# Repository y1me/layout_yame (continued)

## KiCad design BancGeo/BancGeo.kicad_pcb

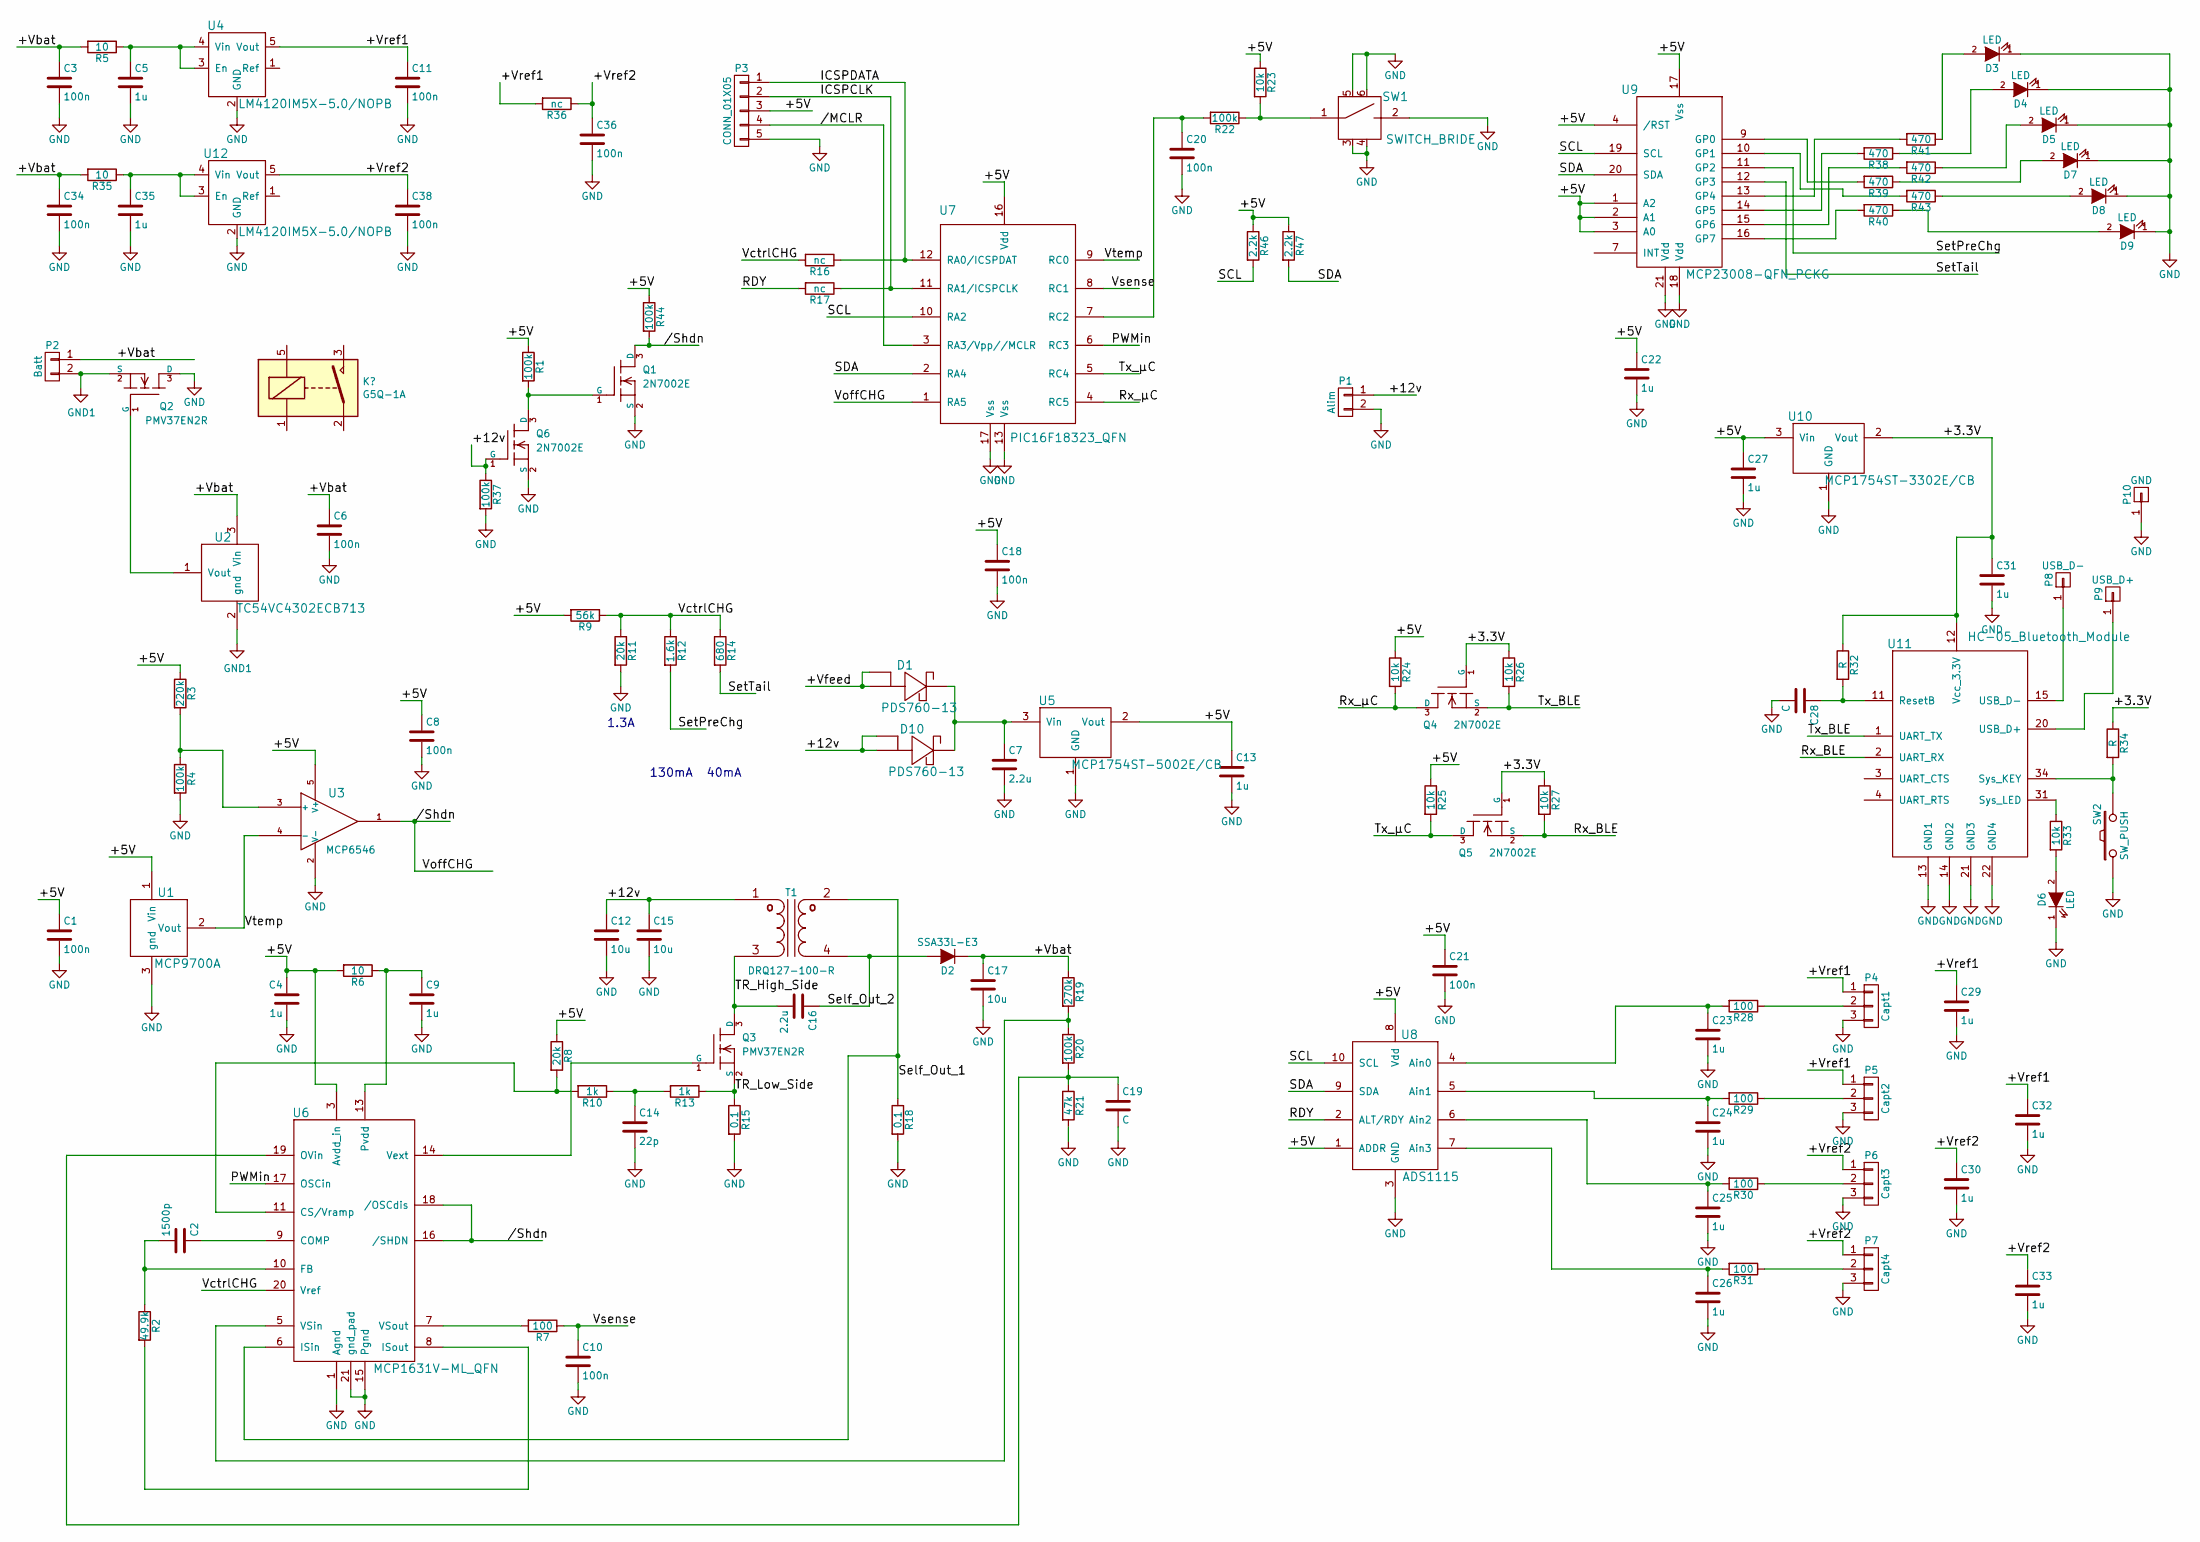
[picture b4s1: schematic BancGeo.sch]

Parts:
C1, C3, C6, C8, C10, C11, C18, C20, C21, C34, C36, C38: 100n; SM0603-MR
C2: 1500p; SM0603-MR
C4, C5, C9, C13, C22, C23, C24, C25, C26, C27, C29, C30, C31, C32, C33, C35: 1u; SM0805-MR
C7, C16: 2.2u; SM0805-MR
C12, C15, C17: 10u; SM0805-MR
C14: 22p; SM0603-MR
C19, C28: C; SM0603-MR
D1, D10: PDS760-13
D2: SSA33L-E3; DO-214AC
D3, D4, D5, D7, D8, D9: LED; LED-5MM_center
D6: LED; LED_0603
P1: Alim; PINHEAD1-2
P2: Batt; PINHEAD1-2
P3: CONN_01X05; HE10_14-5C-2.54-MR
P4: Capt1; PINHEAD1-3
P5: Capt2; PINHEAD1-3
P6: Capt3; PINHEAD1-3
P7: Capt4; PINHEAD1-3
P8: USB_D-; Test_Point_T_H
P9: USB_D+; Test_Point_T_H
P10: GND; Test_Point_T_H
Q1, Q4, Q5, Q6: 2N7002E; SOT23-MR
Q2, Q3: PMV37EN2R; SOT23-MR
R1, R4, R20, R22, R37, R44: 100k; SM0603-MR
R2: 49.9k; SM0603-MR
R3: 220k; SM0603-MR
R5, R6, R35: 10; SM0603-MR
R7, R28, R29, R30, R31: 100; SM0603-MR
R8, R11: 20k; SM0603-MR
R9: 56k; SM0603-MR
R10, R13: 1k; SM0603-MR
R12: 1.6k; SM0603-MR
R14: 680; SM0603-MR
R15, R18: 0.1; SM0603-MR
R16, R17, R36: nc; SM0603-MR
R19: 270k; SM0603-MR
R21: 47k; SM0603-MR
R23, R24, R25, R26, R27, R33: 10k; SM0603-MR
R32, R34: R; SM0603-MR
R38, R39, R40, R41, R42, R43: 470; SM0603-MR
R46, R47: 2.2k
SW1: SWITCH_BRIDE
SW2: SW_PUSH; SW_SPST_B3U-1000P
T1: DRQ127-100-R; DRQ127_CPL_TR
U1: MCP9700A; SOT23-MR
U2: TC54VC4302ECB713; SOT23-MR
U3: MCP6546; SOT23-5-MR
U4, U12: LM4120IM5X-5.0/NOPB; SOT-23-5
U5: MCP1754ST-5002E/CB; SOT23-MR
U6: MCP1631V-ML_QFN; QFN-20-1EP_4x4mm_Pitch0.5mm
U7: PIC16F18323_QFN; QFN-16-1EP_4x4mm_Pitch0.65mm
U8: ADS1115; TSSOP-10_3x3mm_Pitch0.5mm
U9: MCP23008-QFN_PCKG
U10: MCP1754ST-3302E/CB; SOT23-MR
U11: HC-05_Bluetooth_Module

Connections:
/+3.3V: C31.1, Q4.1 (G), Q5.1 (G), R26.1, R27.1, R32.1, R34.1, U10.2 (Vout), U11.12 (Vcc_3.3V)
/+5V: C1.1, C4.1, C8.1, C13.1, C18.1, C21.1, C22.1, C27.1, P3.3, R1.1, R3.1, R6.2, R8.1, R9.2, R23.1, R24.1, R25.1, R44.1, R46.1, R47.1, U1.1 (Vin), U3.5 (V+), U5.2 (Vout), U6.3 (Avdd_in), U7.16 (Vdd), U8.1 (ADDR), U8.8 (Vdd), U9.1 (A2), U9.2 (A1), U9.3 (A0), U9.4 (/RST), U9.17 (Vss), U10.3 (Vin)
/+12v: C12.1, C15.1, D10.A1 (A), D10.A2 (A), P1.1, Q6.1 (G), R37.1, T1.1 (AA)
/+Vbat: C3.1, C6.1, C17.1, C34.1, D2.1 (K), P2.1, R5.2, R19.1, R35.2, U2.3 (Vin)
/+Vref1: C11.1, C29.1, C32.1, P4.1, P5.1, R36.2, U4.5 (Vout)
/+Vref2: C30.1, C33.1, C36.1, C38.1, P6.1, P7.1, R36.1, U12.5 (Vout)
//MCLR: P3.4, U7.3 (RA3/Vpp//MCLR)
//Shdn: Q1.3 (D), R44.2, U3.1, U6.16 (/SHDN), U6.18 (/OSCdis), U7.1 (RA5)
/ICSPCLK: P3.2, R17.1, U7.11 (RA1/ICSPCLK)
/ICSPDATA: P3.1, R16.1, U7.12 (RA0/ICSPDAT)
/PWMin: U6.17 (OSCin), U7.6 (RC3)
/RDY: R17.2, U8.2 (ALT/RDY)
/Rx_BLE: Q5.2 (S), R27.2, U11.2 (UART_RX)
/Rx_µC: Q4.3 (D), R24.2, U7.4 (RC5)
/SCL: R46.2, U7.10 (RA2), U8.10 (SCL), U9.19 (SCL)
/SDA: R47.2, U7.2 (RA4), U8.9 (SDA), U9.20 (SDA)
/Self_Out_1: R18.1, T1.2 (SB), U6.6 (ISin)
/Self_Out_2: C16.1, D2.2 (A), T1.4 (SA)
/SetPreChg: R12.2, U9.11 (GP2)
/SetTail: R14.2, U9.12 (GP3)
/TR_High_Side: C16.2, Q3.3 (D), T1.3 (AB)
/TR_Low_Side: Q3.2 (S), R13.1, R15.1
/Tx_BLE: Q4.2 (S), R26.2, U11.1 (UART_TX)
/Tx_µC: Q5.3 (D), R25.2, U7.5 (RC4)
/VctrlCHG: R9.1, R11.1, R12.1, R14.1, R16.2, U6.20 (Vref)
/Vsense: C10.1, R7.1, U7.8 (RC1)
/Vtemp: U1.2 (Vout), U3.4 (-), U7.9 (RC0)
unnamed: C2.1, U6.9 (COMP)
unnamed: C2.2, R2.1, U6.10 (FB)
unnamed: C5.1, R5.1, U4.3 (En), U4.4 (Vin)
unnamed: C7.1, D1.K, D10.K, U5.3 (Vin)
unnamed: C9.1, R6.1, U6.13 (Pvdd)
unnamed: C14.1, R10.1, R13.2
unnamed: C19.1, R20.2, R21.1, U6.19 (OVin)
unnamed: C20.1, R22.2, U7.7 (RC2)
unnamed: C23.1, R28.2, U8.4 (Ain0)
unnamed: C24.1, R29.2, U8.5 (Ain1)
unnamed: C25.1, R30.2, U8.6 (Ain2)
unnamed: C26.1, R31.2, U8.7 (Ain3)
unnamed: C28.1, R32.2, U11.11 (ResetB)
unnamed: C35.1, R35.1, U12.3 (En), U12.4 (Vin)
unnamed: D1.A1 (A), D1.A2 (A)
unnamed: D3.2 (A), R41.1
unnamed: D4.2 (A), R38.1
unnamed: D5.2 (A), R42.1
unnamed: D6.2 (A), R33.2
unnamed: D7.2 (A), R39.1
unnamed: D8.2 (A), R43.1
unnamed: D9.2 (A), R40.1
unnamed: P4.2, R28.1
unnamed: P5.2, R29.1
unnamed: P6.2, R30.1
unnamed: P7.2, R31.1
unnamed: P8.1, U11.15 (USB_D-)
unnamed: P9.1, U11.20 (USB_D+)
unnamed: Q1.1 (G), Q6.3 (D), R1.2
unnamed: Q2.1 (G), U2.1 (Vout)
unnamed: Q3.1 (G), U6.14 (Vext)
unnamed: R2.2, U6.8 (ISout)
unnamed: R3.2, R4.1, U3.3 (+)
unnamed: R7.2, U6.7 (VSout)
unnamed: R8.2, R10.2, U6.11 (CS/Vramp)
unnamed: R19.2, R20.1, U6.5 (VSin)
unnamed: R22.1, R23.2, SW1.1
unnamed: R33.1, U11.31 (Sys_LED)
unnamed: R34.2, SW2.2, U11.34 (Sys_KEY)
unnamed: R38.2, U9.14 (GP5)
unnamed: R39.2, U9.9 (GP0)
unnamed: R40.2, U9.16 (GP7)
unnamed: R41.2, U9.13 (GP4)
unnamed: R42.2, U9.15 (GP6)
unnamed: R43.2, U9.10 (GP1)

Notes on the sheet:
1.3A
130mA
40mA

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
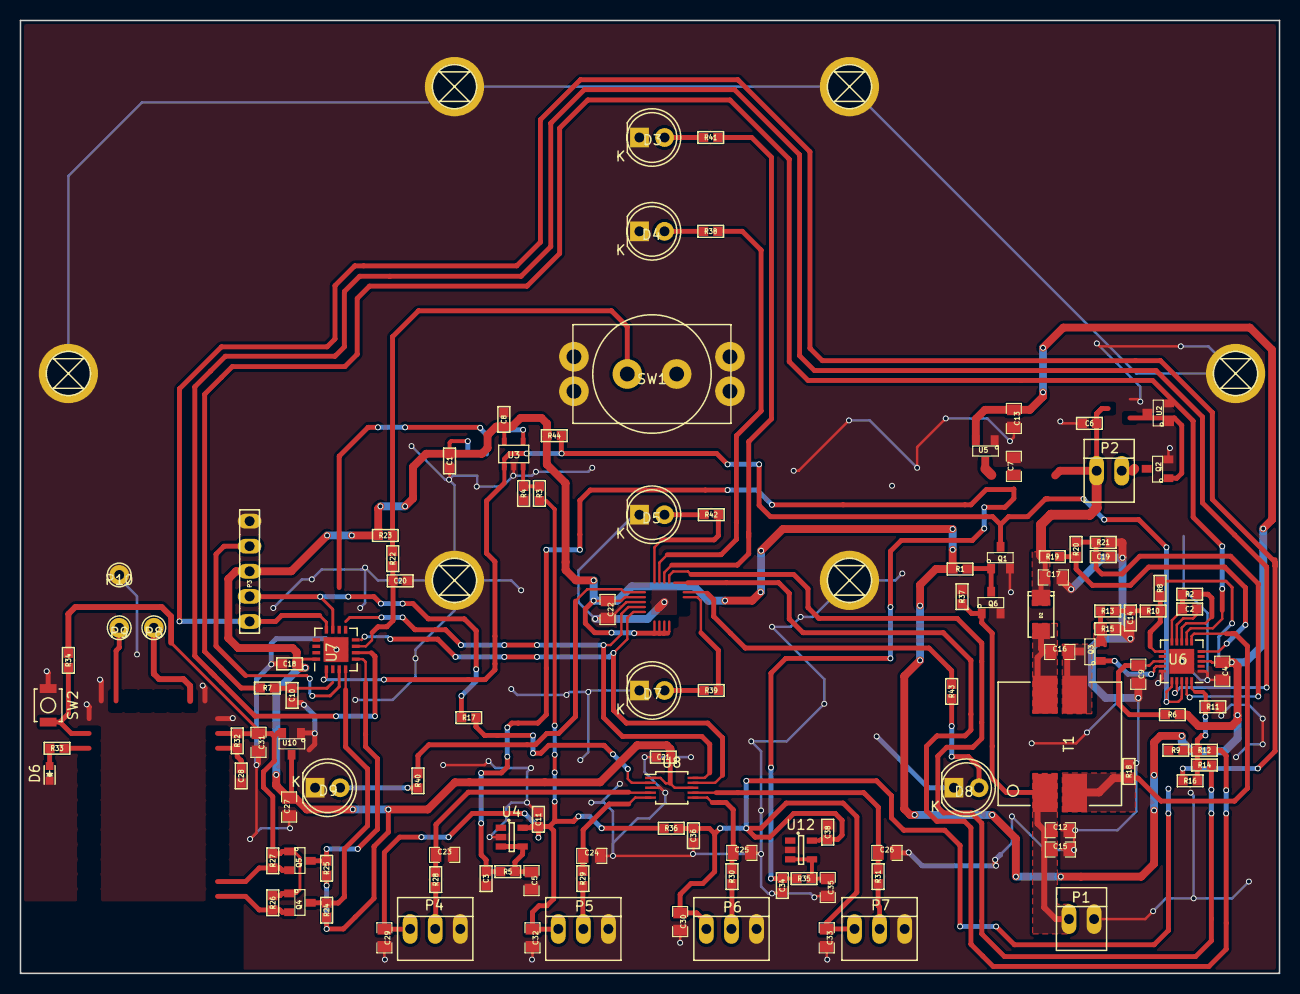
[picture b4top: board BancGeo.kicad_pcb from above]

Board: 2 copper layers, 127.5 x 96.5 mm, 118 parts (1 on the bottom side), 61 nets.

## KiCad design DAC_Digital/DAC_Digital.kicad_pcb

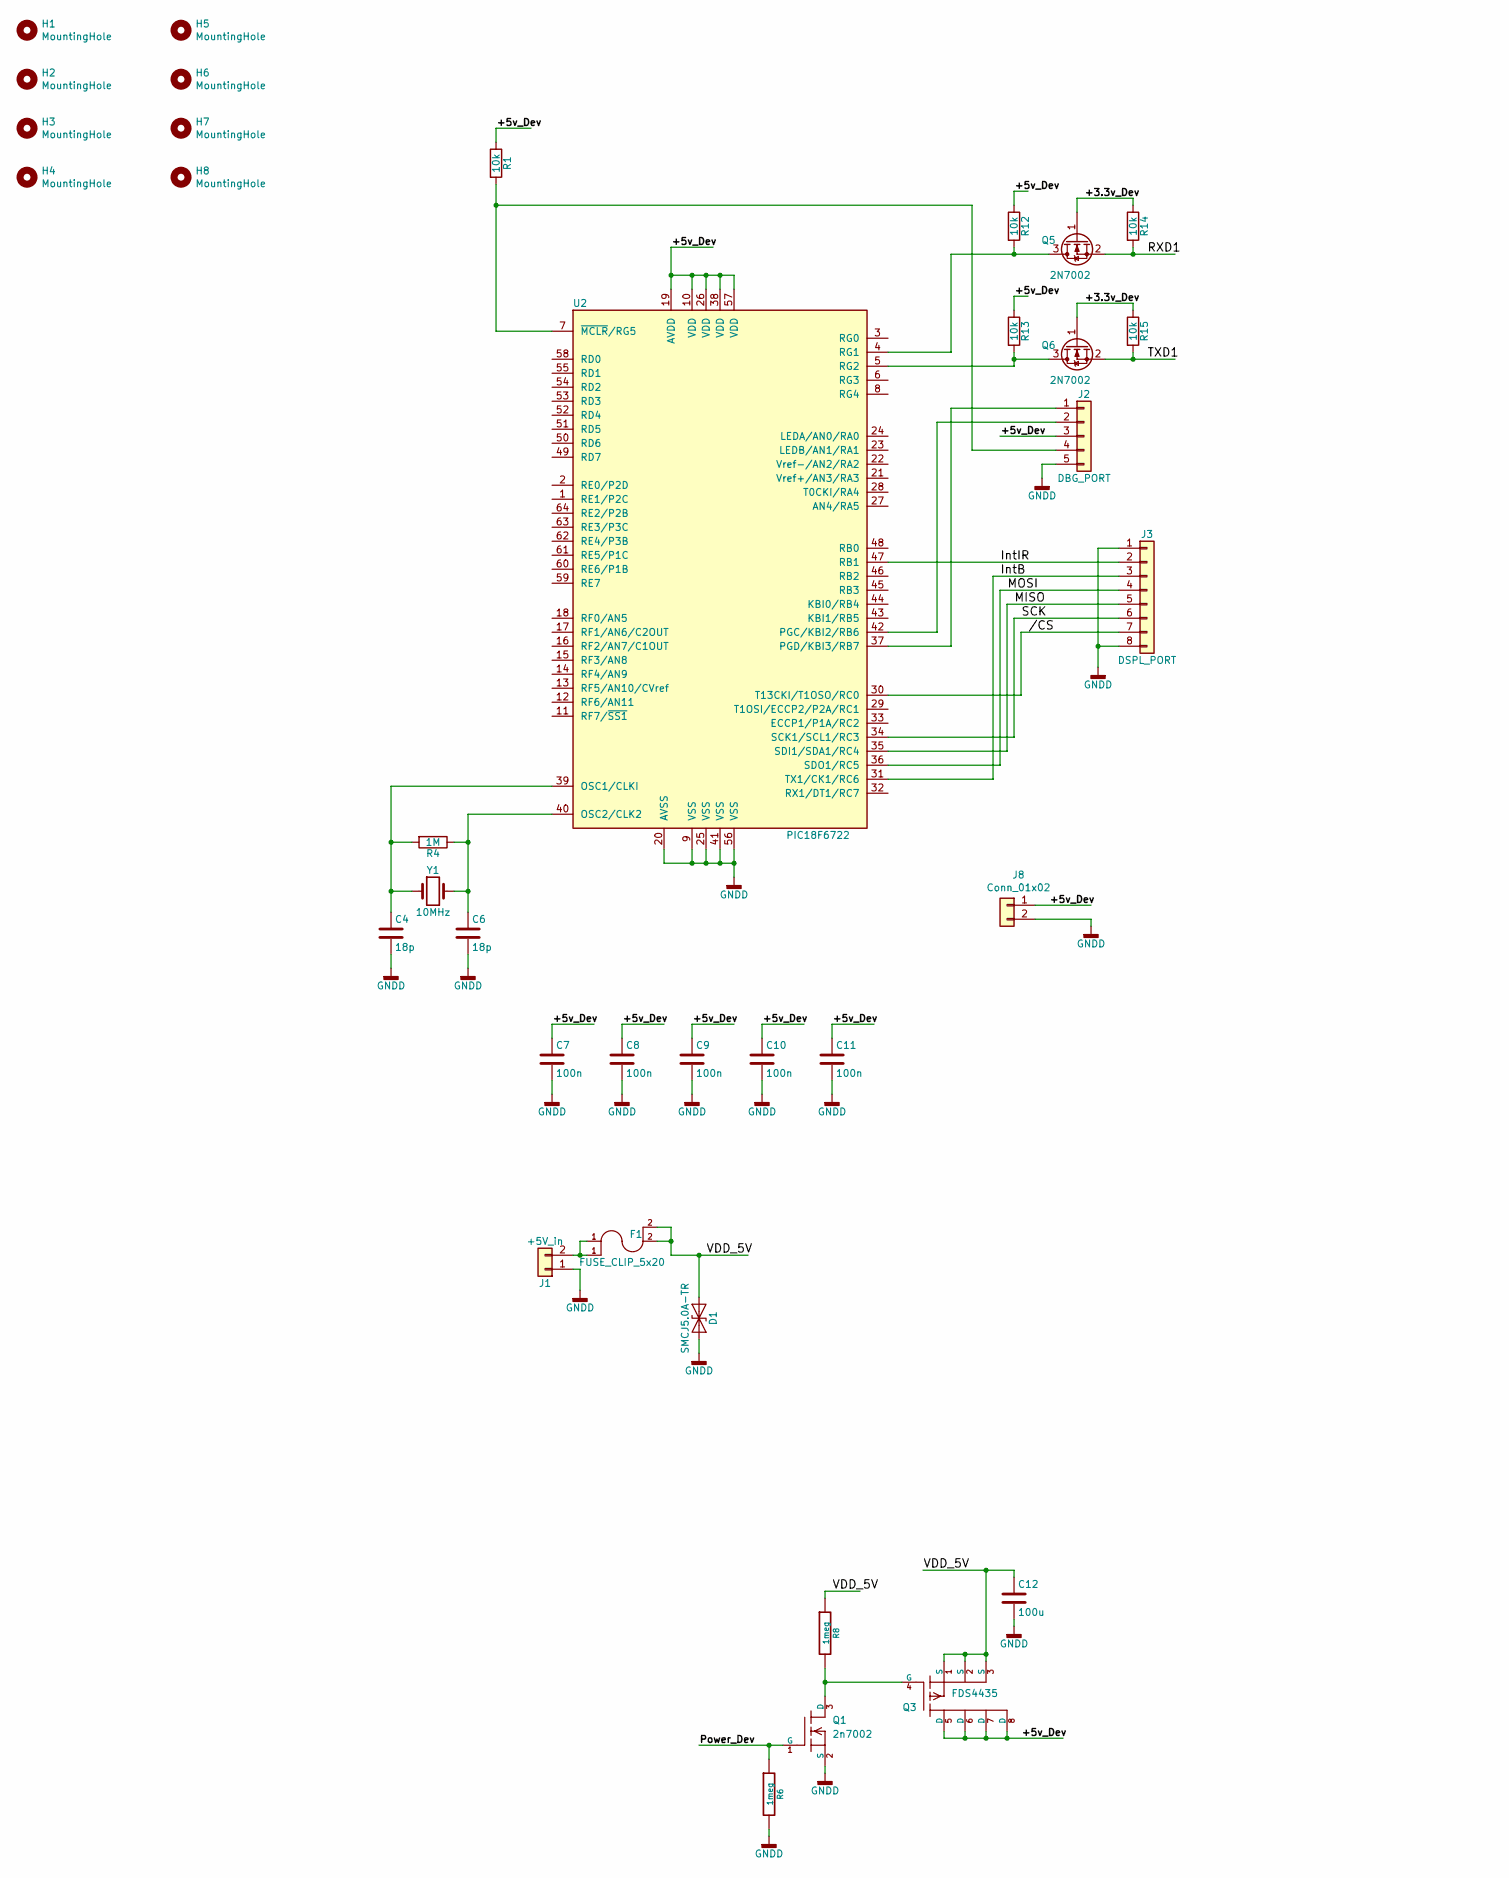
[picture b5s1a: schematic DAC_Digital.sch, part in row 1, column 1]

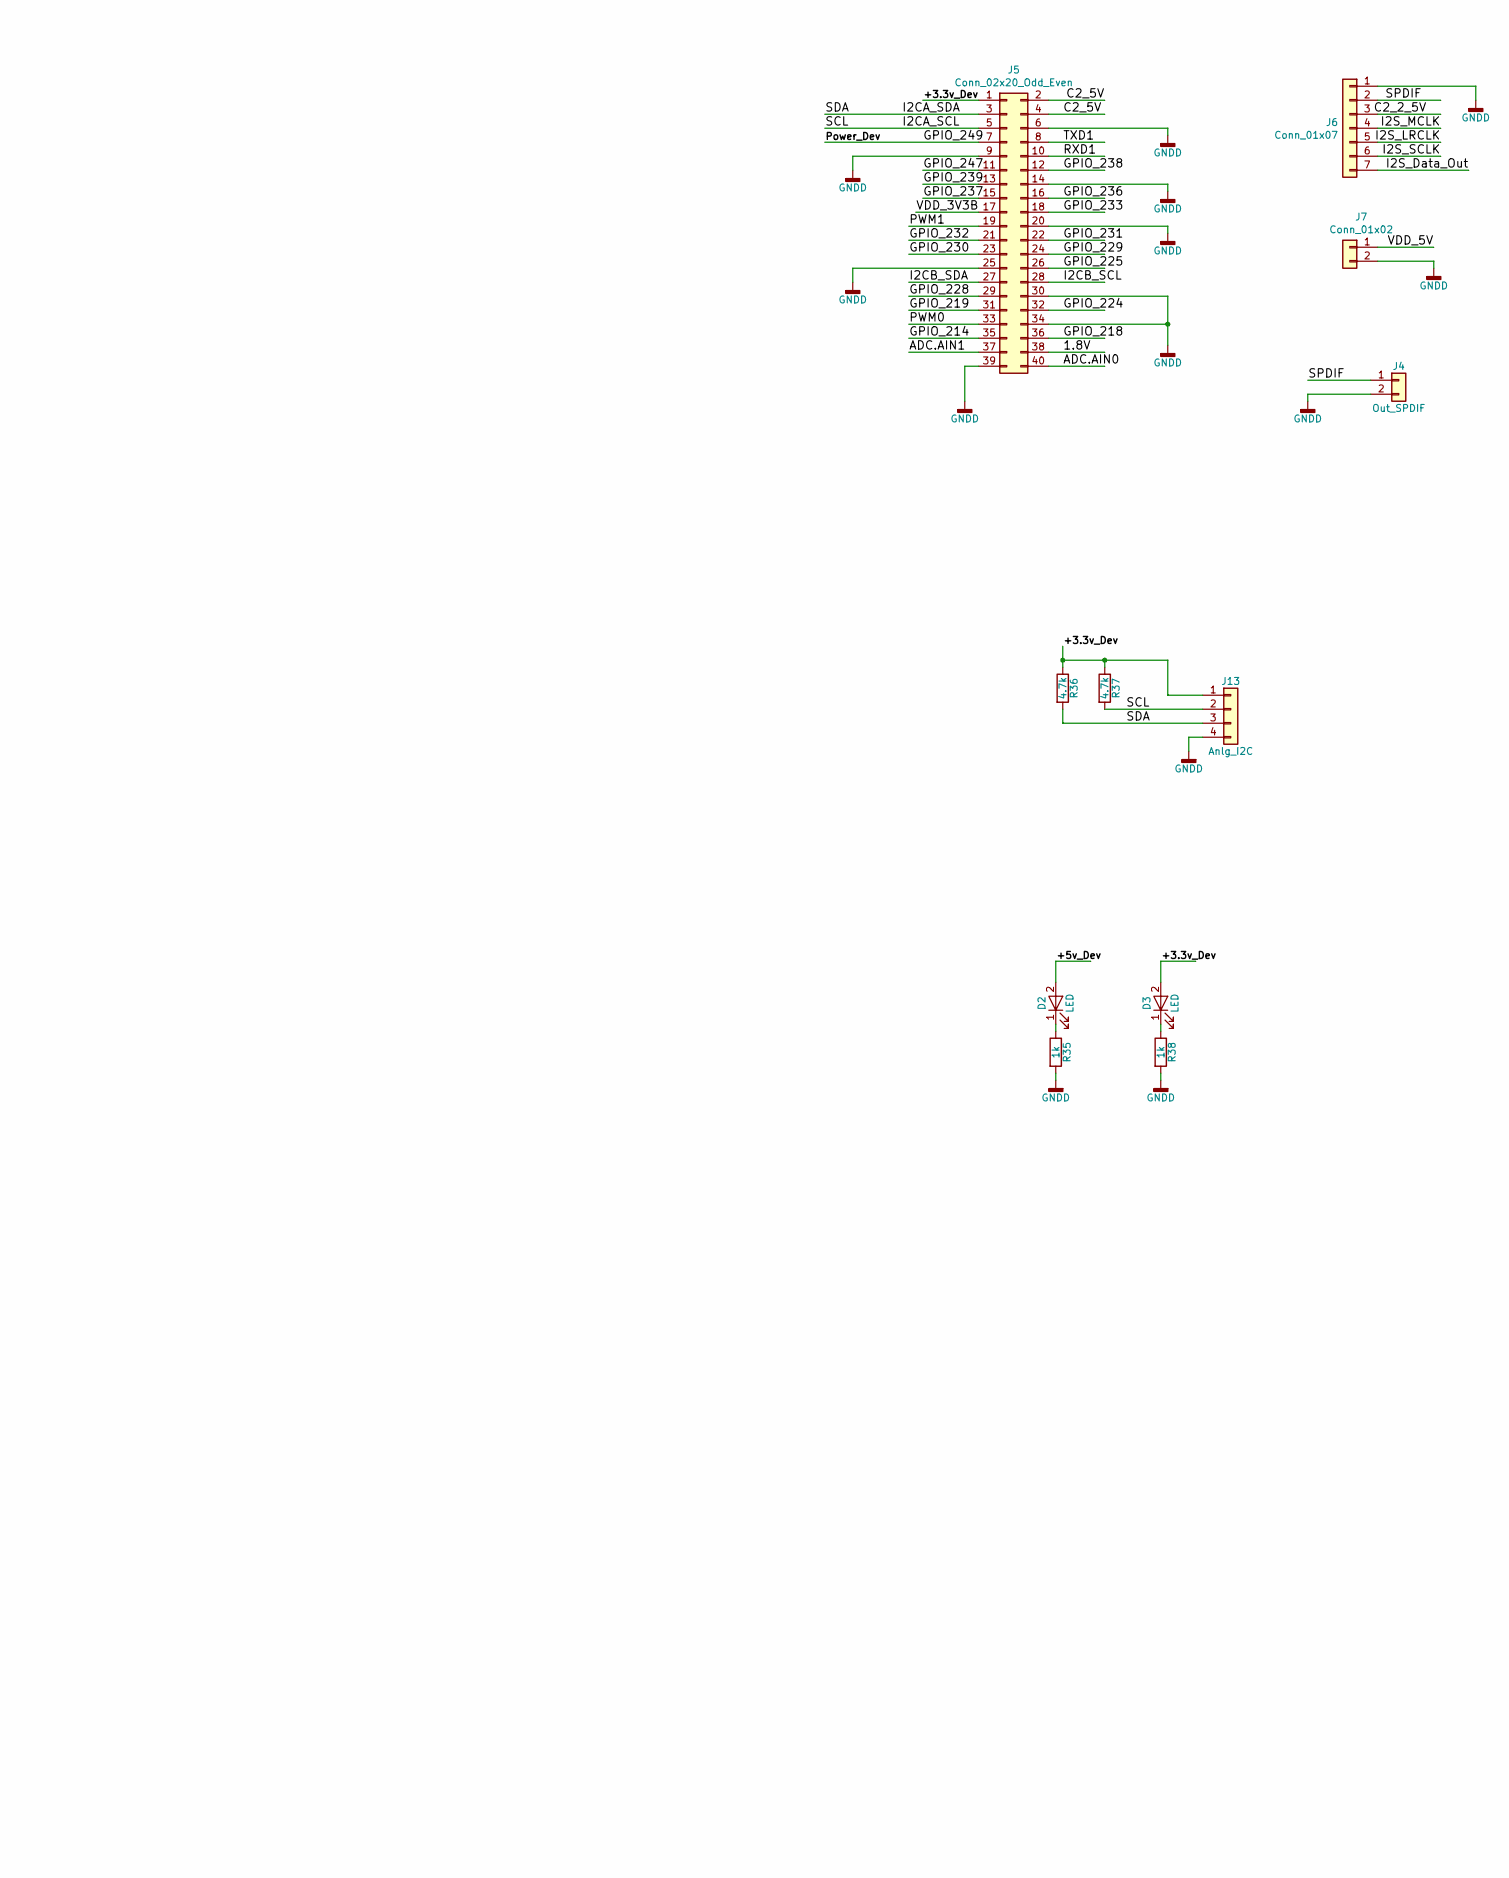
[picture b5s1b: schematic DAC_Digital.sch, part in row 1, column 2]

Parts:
C4, C6: 18p; R_0603_1608Metric
C7, C8, C9, C10, C11: 100n; R_0603_1608Metric
C12: 100u; CP_Tantalum_Case-U_EIA-6032-15_Hand; Tolerance (%) 16
D1: SMCJ5.0A-TR; D_SMC
D2, D3: LED; LED_0603_1608Metric
F1: FUSE_CLIP_5x20; Fuse_5x20
H1, H2, H3, H4: MountingHole; MountingHole_3.2mm_M3_DIN965_Pad
H5, H6, H7, H8: MountingHole; MountingHole_3.2mm_M3_DIN965
J1: +5V_in; TerminalBlock_bornier-2_P5.08mm
J2: DBG_PORT; PinHeader_1x05_P2.54mm_Horizontal
J3: DSPL_PORT; PinHeader_1x08_P2.54mm_Horizontal
J4: Out_SPDIF; PinHeader_1x02_P2.54mm_Vertical
J5: Conn_02x20_Odd_Even; PinSocket_2x20_P2.54mm_Vertical
J6: Conn_01x07; PinSocket_1x07_P2.54mm_Vertical
J7, J8: Conn_01x02; PinHeader_1x02_P2.54mm_Vertical
J13: Anlg_I2C; PinHeader_1x04_P2.54mm_Vertical
Q1: 2n7002; SOT-23
Q3: FDS4435; SO-8_5.3x6.2mm_P1.27mm
Q5, Q6: 2N7002; SOT-23
R1, R12, R13, R14, R15: 10k; R_0603_1608Metric
R4: 1M; R_0603_1608Metric
R6, R8: 1meg; R_0603_1608Metric
R35, R38: 1k; R_0603_1608Metric
R36, R37: 4.7k; R_0603_1608Metric
U2: PIC18F6722; TQFP-64_10x10mm_Pitch0.5mm
Y1: 10MHz; Crystal_HC49-U_Vertical

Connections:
/1.8V: J5.38
/+3.3v_Dev: D3.2 (A), J5.1, J13.1, Q5.1 (G), Q6.1 (G), R14.1, R15.1, R36.1, R37.1
/+5v_Dev: C7.1, C8.1, C9.1, C10.1, C11.1, D2.2 (A), J2.3, J8.1, Q3.5 (D), Q3.6 (D), Q3.7 (D), Q3.8 (D), R1.1, R12.1, R13.1, U2.10 (VDD), U2.19 (AVDD), U2.26 (VDD), U2.38 (VDD), U2.57 (VDD)
//CS: J3.7, U2.30 (T13CKI/T1OSO/RC0)
/ADC.AIN0: J5.40
/ADC.AIN1: J5.37
/C2_2_5V: J6.3
/C2_5V: J5.2, J5.4
/GPIO_214: J5.35
/GPIO_218: J5.36
/GPIO_219: J5.31
/GPIO_224: J5.32
/GPIO_225: J5.26
/GPIO_228: J5.29
/GPIO_229: J5.24
/GPIO_230: J5.23
/GPIO_231: J5.22
/GPIO_232: J5.21
/GPIO_233: J5.18
/GPIO_236: J5.16
/GPIO_237: J5.15
/GPIO_238: J5.12
/GPIO_239: J5.13
/GPIO_247: J5.11
/GPIO_249: J5.7, Q1.1 (G), R6.1
/I2CA_SCL: J5.5, J13.2, R37.2
/I2CA_SDA: J5.3, J13.3, R36.2
/I2CB_SCL: J5.28
/I2CB_SDA: J5.27
/I2S_Data_Out: J6.7
/I2S_LRCLK: J6.5
/I2S_MCLK: J6.4
/I2S_SCLK: J6.6
/IntB: J3.3, U2.31 (TX1/CK1/RC6)
/IntIR: J3.2, U2.47 (RB1)
/MISO: J3.5, U2.35 (SDI1/SDA1/RC4)
/MOSI: J3.4, U2.36 (SDO1/RC5)
/PWM0: J5.33
/PWM1: J5.19
/RXD1: J5.10, Q5.2 (S), R14.2
/SCK: J3.6, U2.34 (SCK1/SCL1/RC3)
/SPDIF: J4.1, J6.2
/TXD1: J5.8, Q6.2 (S), R15.2
/VDD_3V3B: J5.17
/VDD_5V: C12.1, D1.1 (A1), F1.2, J7.1, Q3.1 (S), Q3.2 (S), Q3.3 (S), R8.1
GNDD: C4.2, C6.2, C7.2, C8.2, C9.2, C10.2, C11.2, C12.2, D1.2 (A2), J1.1, J2.5, J3.1, J3.8, J4.2, J5.6, J5.9, J5.14, J5.20, J5.25, J5.30, J5.34, J5.39, J6.1, J7.2, J8.2, J13.4, Q1.2 (S), R6.2, R35.2, R38.2, U2.9 (VSS), U2.20 (AVSS), U2.25 (VSS), U2.41 (VSS), U2.56 (VSS)
unnamed: C4.1, R4.2, U2.39 (OSC1/CLKI), Y1.1
unnamed: C6.1, R4.1, U2.40 (OSC2/CLK2), Y1.2
unnamed: D2.1 (K), R35.1
unnamed: D3.1 (K), R38.1
unnamed: F1.1, J1.2
unnamed: J2.1, U2.37 (PGD/KBI3/RB7)
unnamed: J2.2, U2.42 (PGC/KBI2/RB6)
unnamed: J2.4, R1.2, U2.7 (~MCLR~/RG5)
unnamed: Q1.3 (D), Q3.4 (G), R8.2
unnamed: Q5.3 (D), R12.2, U2.4 (RG1)
unnamed: Q6.3 (D), R13.2, U2.5 (RG2)

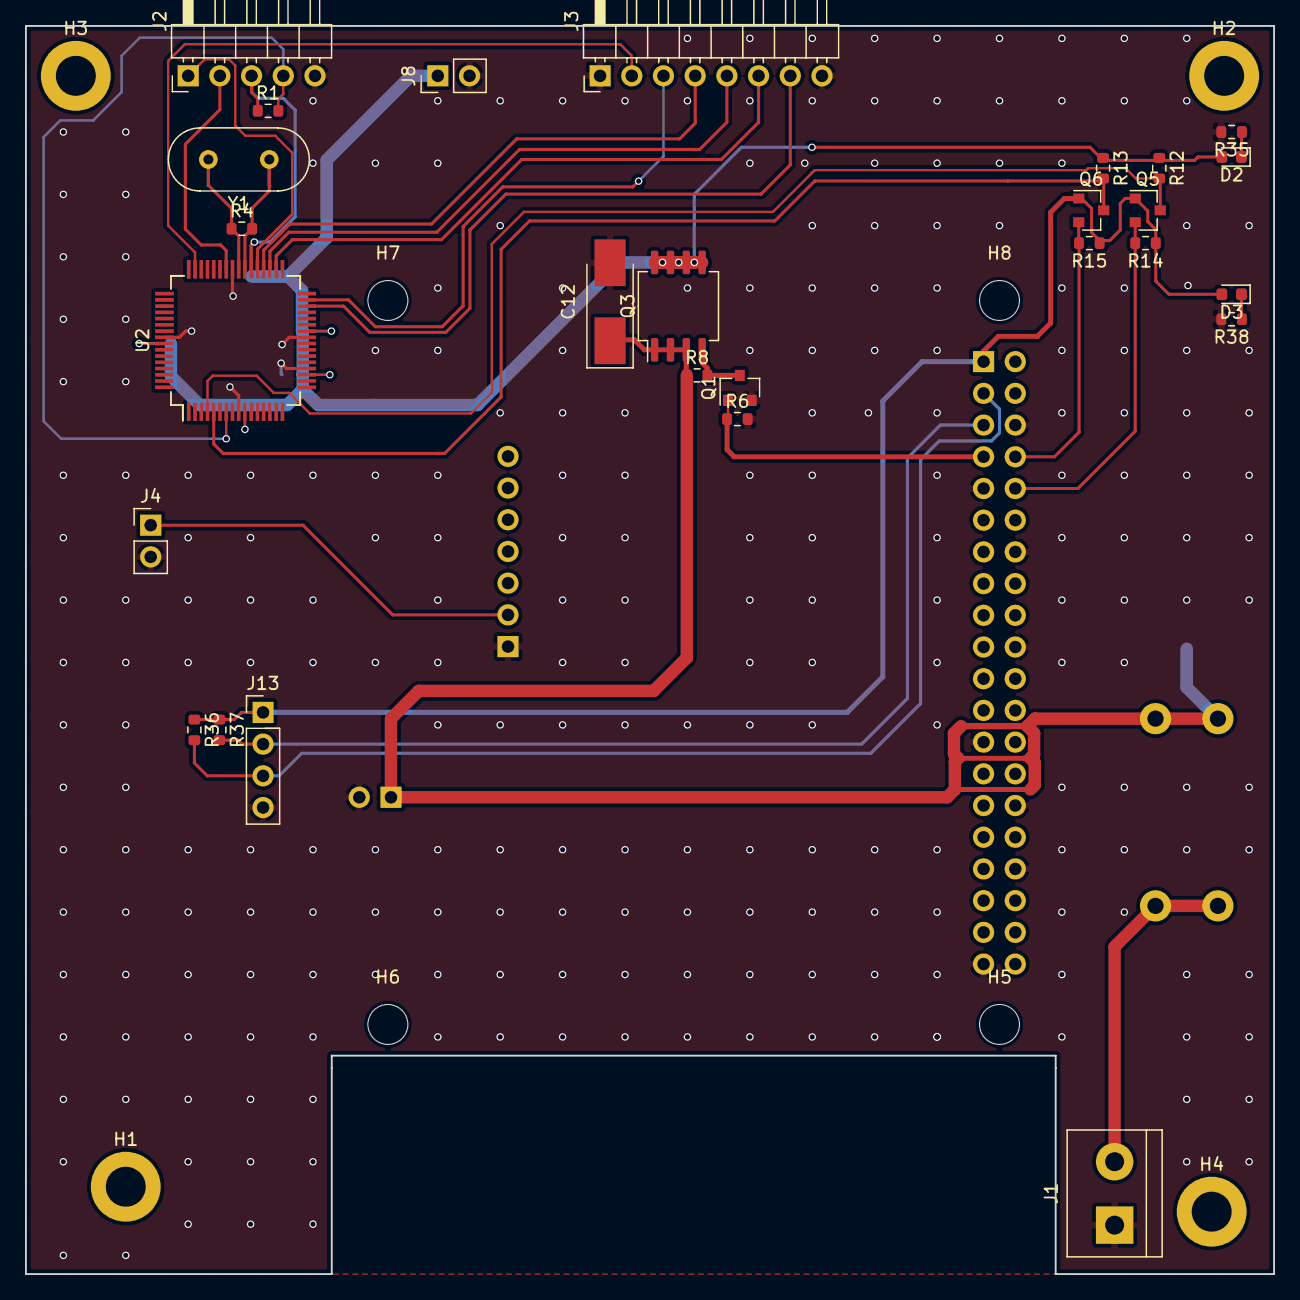
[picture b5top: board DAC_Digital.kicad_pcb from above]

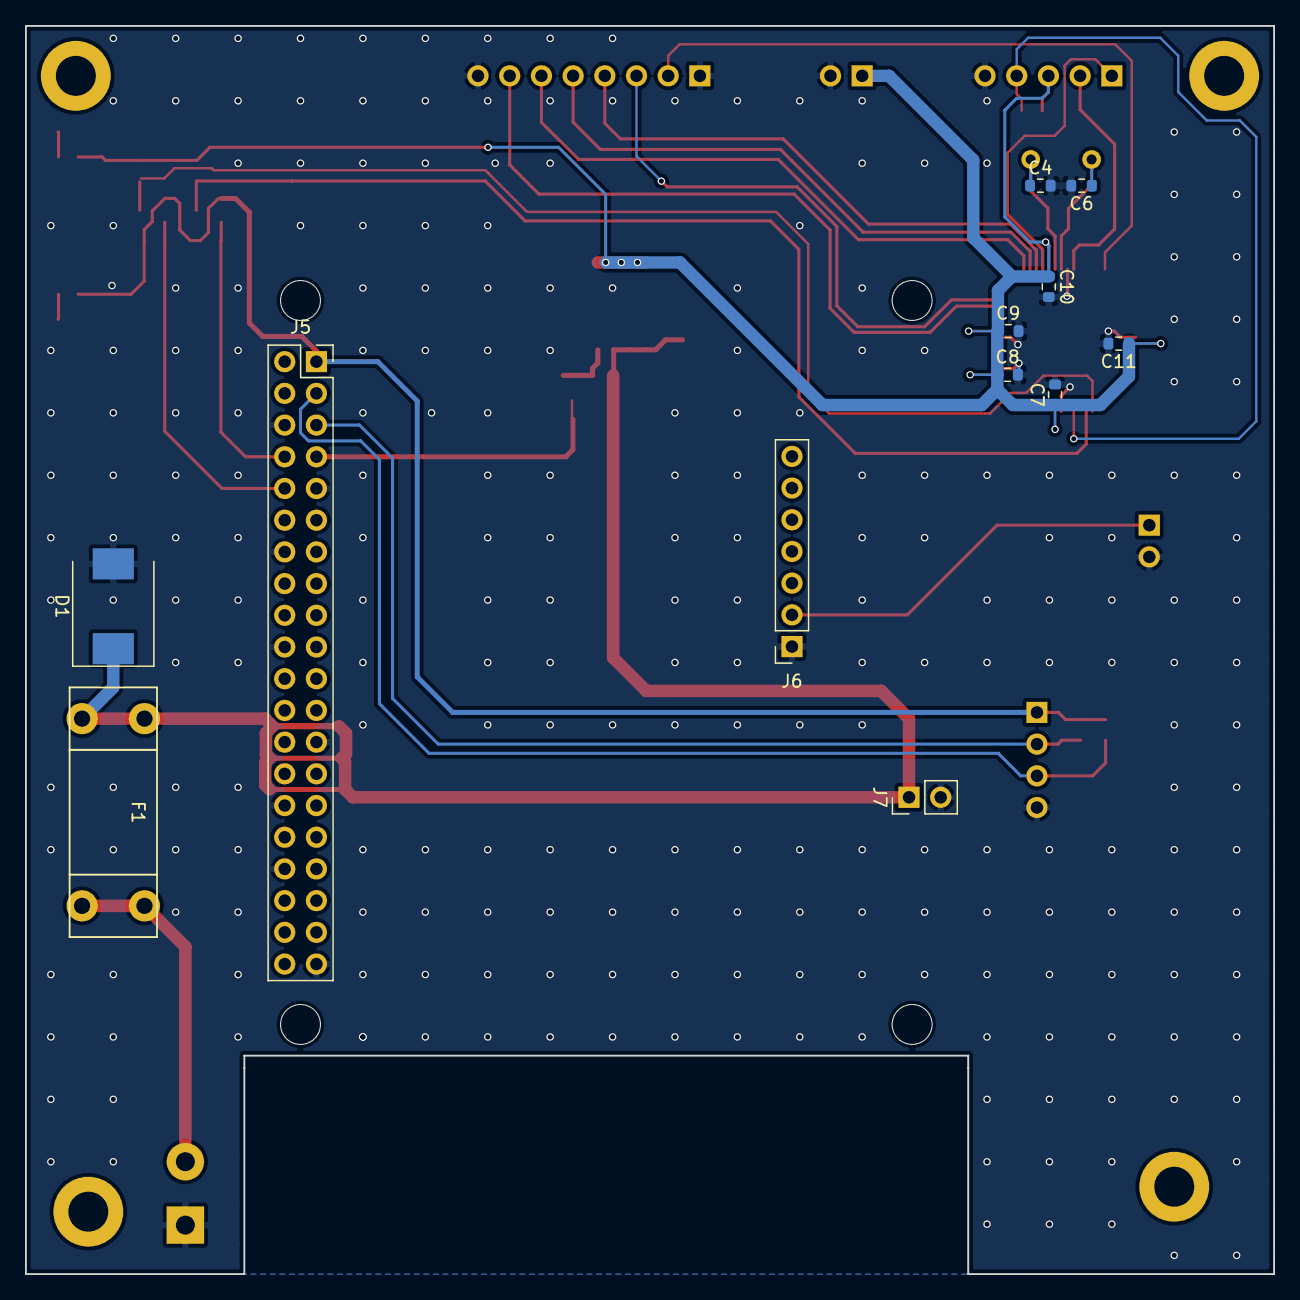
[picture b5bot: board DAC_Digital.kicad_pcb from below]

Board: 2 copper layers, 100.0 x 100.0 mm, 47 parts (12 on the bottom side), 28 nets.

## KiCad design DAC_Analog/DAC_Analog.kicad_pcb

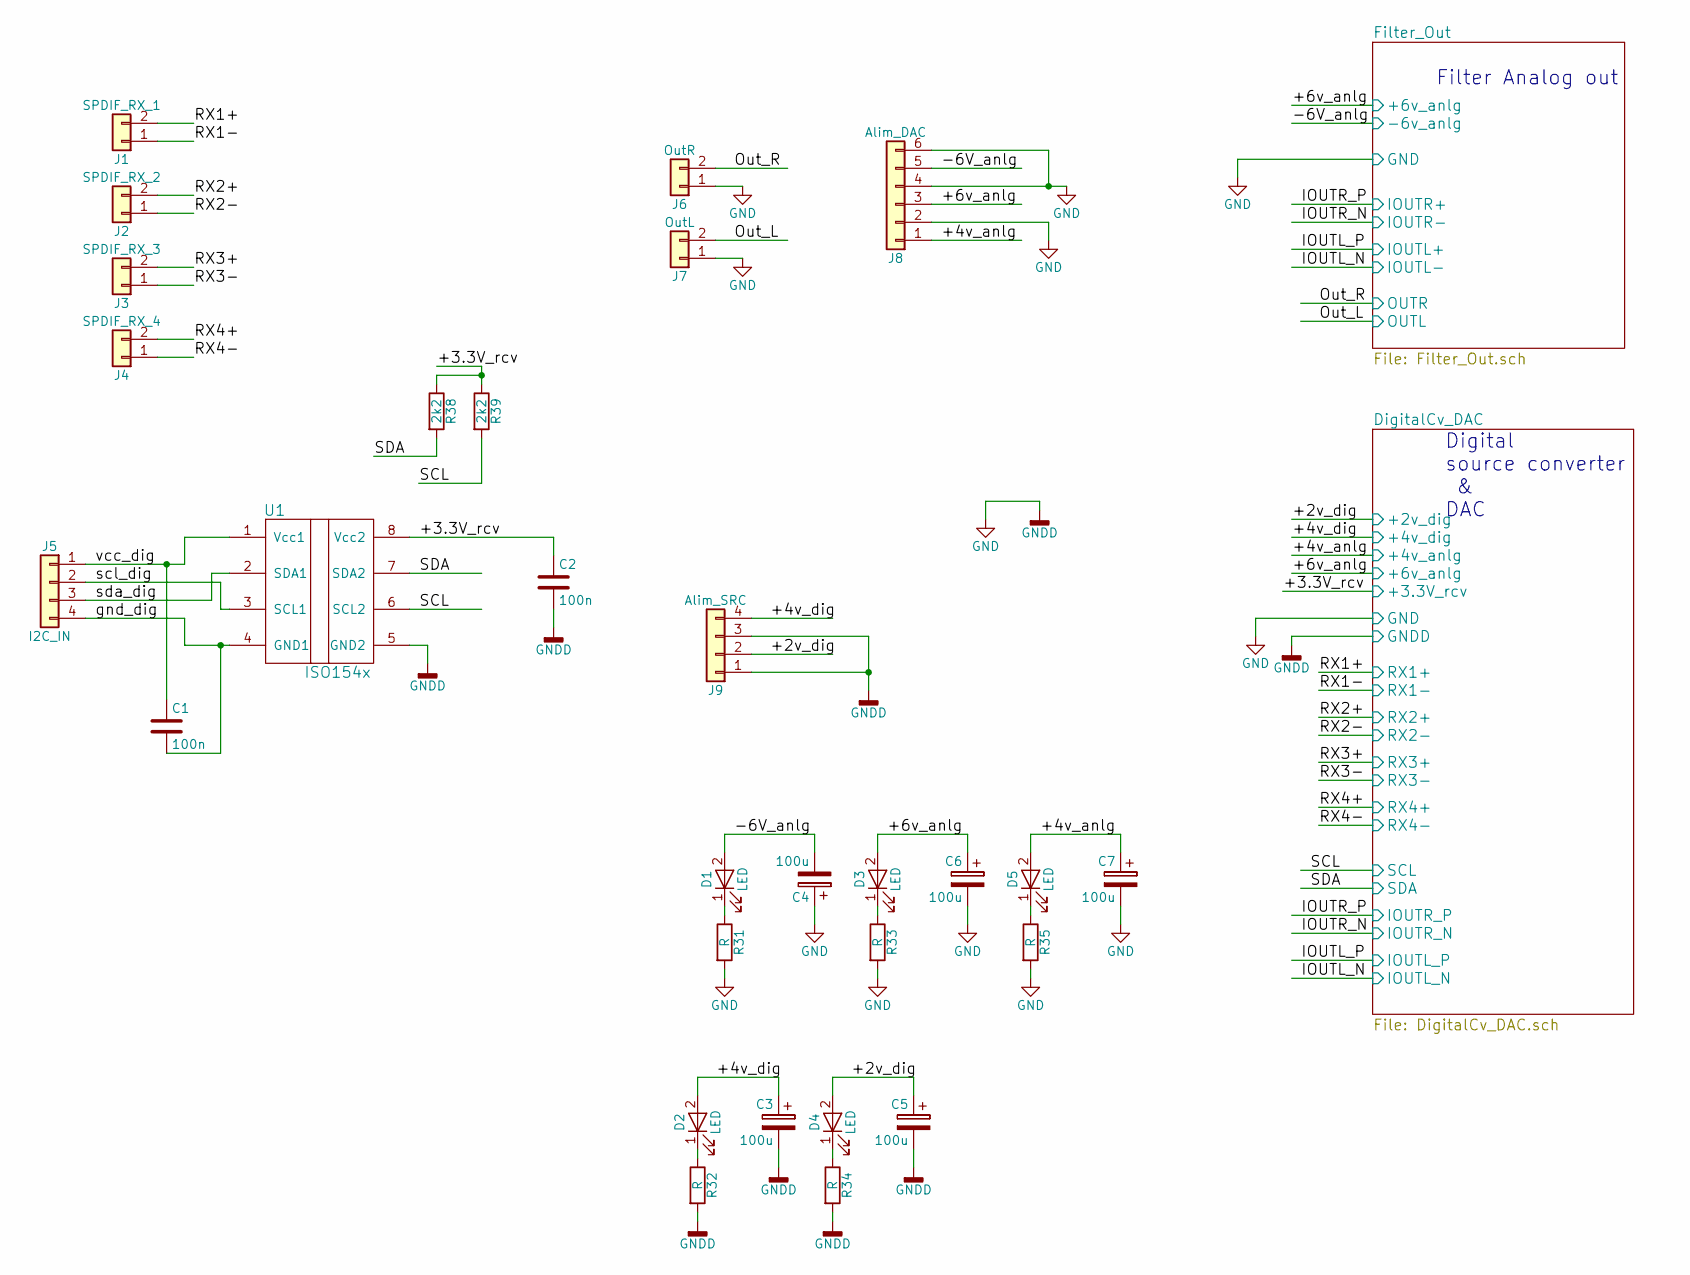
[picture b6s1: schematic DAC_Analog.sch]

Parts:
C1, C2: 100n; SM0603-MR
C3, C4, C5, C6, C7: 100u; CP_Tantalum_Case-C_EIA-6032-28_Hand
D1, D2, D3, D4, D5: LED; SM0603-LED-MR
J1: SPDIF_RX_1; Pin_Header_Straight_1x02_Pitch2.54mm
J2: SPDIF_RX_2; Pin_Header_Straight_1x02_Pitch2.54mm
J3: SPDIF_RX_3; Pin_Header_Straight_1x02_Pitch2.54mm
J4: SPDIF_RX_4; Pin_Header_Straight_1x02_Pitch2.54mm
J5: I2C_IN; Pin_Header_Straight_1x04_Pitch2.54mm
J6: OutR; Pin_Header_Straight_1x02_Pitch2.54mm
J7: OutL; Pin_Header_Straight_1x02_Pitch2.54mm
J8: Alim_DAC; Pin_Header_Straight_1x06_Pitch2.54mm
J9: Alim_SRC; Pin_Header_Straight_1x04_Pitch2.54mm
R31, R32, R33, R34, R35: R; SM0603-MR
R38, R39: 2k2; SM0603-MR
U1: ISO154x; SOIC-8_3.9x4.9mm_Pitch1.27mm

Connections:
/+2v_dig: C5.1, D4.2 (A), J9.2; also elsewhere on the board
/+3.3V_rcv: C2.1, R38.1, R39.1, U1.8 (Vcc2); also elsewhere on the board
/+4v_anlg: C7.1, D5.2 (A), J8.1; also elsewhere on the board
/+4v_dig: C3.1, D2.2 (A), J9.4; also elsewhere on the board
/+6v_anlg: C6.1, D3.2 (A), J8.3; also elsewhere on the board
/-6V_anlg: C4.2, D1.2 (A), J8.5; also elsewhere on the board
/Out_L: J7.2; also elsewhere on the board
/Out_R: J6.2; also elsewhere on the board
/RX1+: J1.2; also elsewhere on the board
/RX1-: J1.1; also elsewhere on the board
/RX2+: J2.2; also elsewhere on the board
/RX2-: J2.1; also elsewhere on the board
/RX3+: J3.2; also elsewhere on the board
/RX3-: J3.1; also elsewhere on the board
/RX4+: J4.2; also elsewhere on the board
/RX4-: J4.1; also elsewhere on the board
/SCL: R39.2, U1.6 (SCL2); also elsewhere on the board
/SDA: R38.2, U1.7 (SDA2); also elsewhere on the board
/gnd_dig: C1.2, J5.4, U1.4 (GND1)
/scl_dig: J5.2, U1.3 (SCL1)
/sda_dig: J5.3, U1.2 (SDA1)
/vcc_dig: C1.1, J5.1, U1.1 (Vcc1)
GND: C2.2, C3.2, C4.1, C5.2, C6.2, C7.2, J6.1, J7.1, J8.2, J8.4, J8.6, J9.1, J9.3, R31.2, R32.2, R33.2, R34.2, R35.2, U1.5 (GND2); also elsewhere on the board
unnamed: D1.1 (K), R31.1
unnamed: D2.1 (K), R32.1
unnamed: D3.1 (K), R33.1
unnamed: D4.1 (K), R34.1
unnamed: D5.1 (K), R35.1

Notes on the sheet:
Filter Analog out
Digital source converter & DAC
